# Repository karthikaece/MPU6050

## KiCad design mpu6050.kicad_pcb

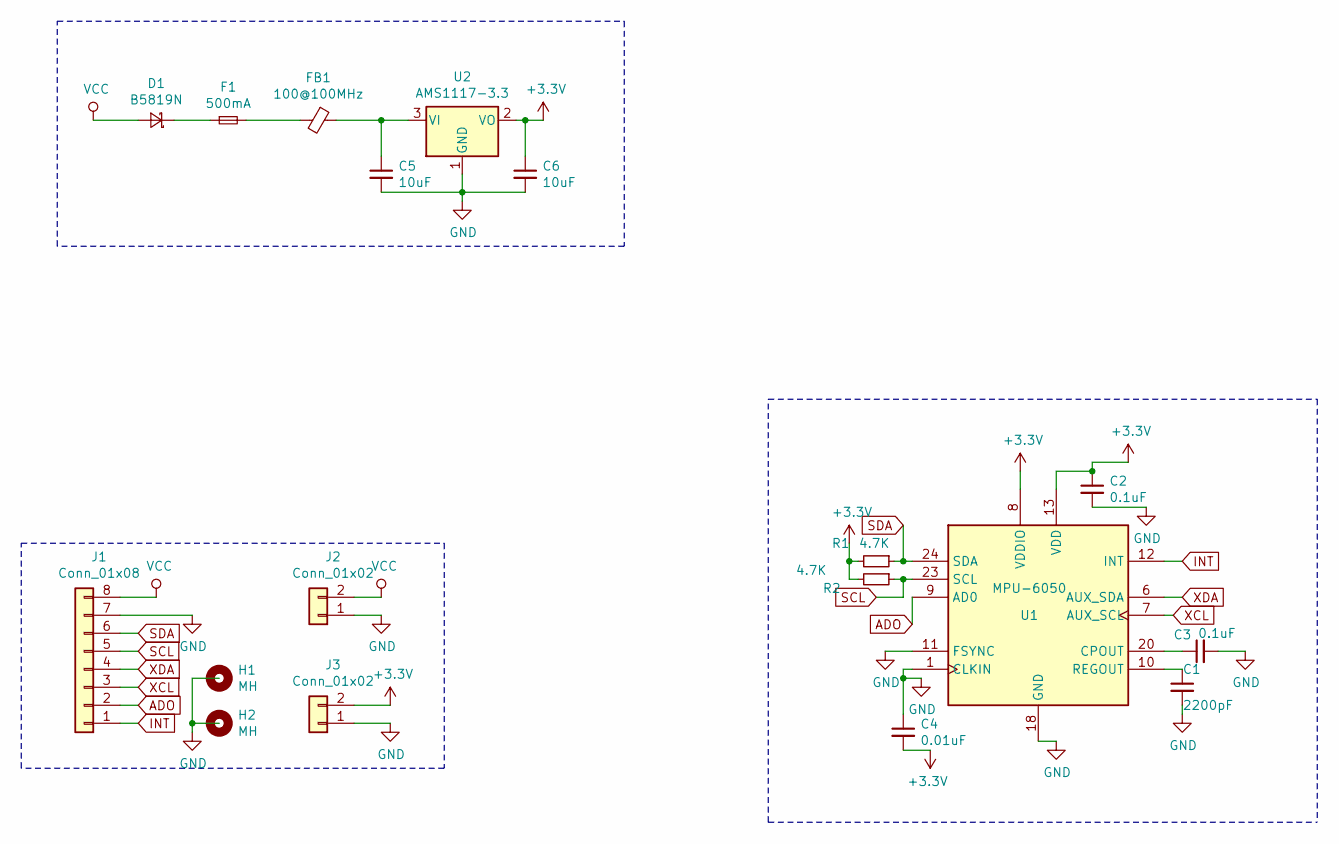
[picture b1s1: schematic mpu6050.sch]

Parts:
C1: 2200pF; C_0402_1005Metric
C2, C3: 0.1uF; C_0402_1005Metric
C4: 0.01uF; C_0402_1005Metric
C5, C6: 10uF; C_0402_1005Metric
D1: B5819N; D_SOD-123
F1: 500mA; Fuse_0603_1608Metric
FB1: 100@100MHz; L_0603_1608Metric
H1, H2: MH; MountingHole_3.2mm_M3
J1: Conn_01x08; PinHeader_1x08_P2.54mm_Vertical
J2, J3: Conn_01x02; PinHeader_1x02_P2.54mm_Vertical
R1, R2: 4.7K; R_0402_1005Metric
U1: MPU-6050; InvenSense_QFN-24_4x4mm_P0.5mm
U2: AMS1117-3.3; SOT-223-3_TabPin2

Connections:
+3V3: C2.1, C4.2, C6.1, J3.2, R1.2, R2.2, U1.8 (VDDIO), U1.13 (VDD), U2.2 (VO)
ADO: J1.2, U1.9 (AD0)
GND: C1.2, C2.2, C3.2, C4.1, C5.2, C6.2, J1.7, J2.1, J3.1, U1.1 (CLKIN), U1.11 (FSYNC), U1.18 (GND), U2.1 (GND)
INT: J1.1, U1.12 (INT)
unnamed: C1.1, U1.10 (REGOUT)
unnamed: C3.1, U1.20 (CPOUT)
unnamed: C5.1, FB1.1, U2.3 (VI)
unnamed: D1.1 (K), F1.1
unnamed: F1.2, FB1.2
SCL: J1.5, R2.1, U1.23 (SCL)
SDA: J1.6, R1.1, U1.24 (SDA)
VCC: D1.2 (A), J1.8, J2.2
XCL: J1.3, U1.7 (AUX_SCL)
XDA: J1.4, U1.6 (AUX_SDA)

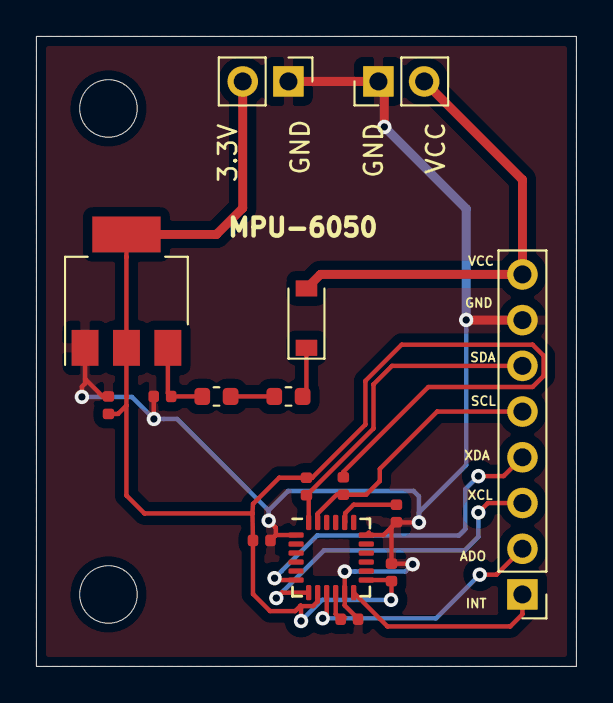
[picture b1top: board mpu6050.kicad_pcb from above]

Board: 2 copper layers, 30.0 x 35.0 mm, 18 parts (0 on the bottom side), 14 nets.
